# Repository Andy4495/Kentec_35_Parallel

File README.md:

# Kentec EB-LM4F120-L35 BoosterPack Library

This library supports the Kentec [EB-LM4F120-L35][4] 3.5" QVGA TFT LCD BoosterPack with Parallel I/O.

The EB-LM4F120-L35 uses the same display and controller chip as the SPI-based [BOOSTXL-K350QVG-S1][5] BoosterPack.

The parallel I/O of the LM4F120 version of the BoosterPack allows faster screen drawing with the disadvantage of requiring more I/O pins. Although the name implies that it was designed for the Stellaris ARM-based LaunchPad, it will work with MSP430-based LaunchPads that have the 40-pin BOOSTXL interface and enough RAM to support using a large display.

This library is optimized for use with the [MSP430F5529][9] and [MSP432P401R][10] LaunchPads, but will also work with any other MSP or Tiva LaunchPad with the BOOSTXL interface. Display refresh rates on boards other than the F5529 or MSP432 will be much slower due to the use of the generic `DigitalWrite()` for I/O control. When used with the F5529 or MSP432, the library uses a much faster direct register control for I/O.

This library is based on the [Kentec_35_SPI library][8] which is included with Energia.

The screen touch functionality was carried over from the SPI version of the library and the I/O pin number definitions were updated accordingly. However, touch functionality has not been tested with this library.

## Usage

See the sketch included in the `examples` folder.

The parallel library works the same as the built-in SPI version of the library. See the [Reference Manual][12] included with the library.

## Specialized Interface Board

I created a custom interface board to change the mapping of the pins between the Kentec BoosterPack and the F5529 LaunchPad. This was done for two reasons:

- Directly map the data bit positions of the Kentec controller interface to the MSP port bit positions. This allows simplification of the library code to allow even faster screen refresh rates.
- Move the Kentec pins to the inner BOOSTXL header pins (J3 and J4), so that the standard BoosterPack I/O pins are available for other devices (e.g. SPI and I2C pins).

Details on the board design can be found in the [extras/Hardware][11] folder.

The library has been modified to support the interface board. When using the library with the interface, the only code change needed is in the constructor to let the library know that the interface board is connected. By default, the TOUCH functionality is not connected when using the interface board:

    Screen_K35_Parallel myScreen(Screen_K35_Parallel::F5529_INTERFACE_BOARD_INSTALLED, Screen_K35_Parallel::TOUCH_DISABLED);

If, however, you connect the TOUCH sensor pins (XP->P2, YP->P6, XN->P12, YN->P11), then use the following constructor:

    Screen_K35_Parallel myScreen(Screen_K35_Parallel::F5529_INTERFACE_BOARD_INSTALLED, Screen_K35_Parallel::TOUCH_ENABLED);

## References

- EB-LM4F120-L35 BoosterPack [product page][4]
- EB-LM4F120-L35 BoosterPack [user guide][1]
- SSD2119 driver chip [datasheet][2]
- [Review][3] of the EB-LM4F120-L35 from Rei Vilo's Embedded Computing site.
- Kentec_35_SPI library suite [description][8] and [source][6].
- BOOSTXL-K350QVG-S1 (SPI) [product page][7]

## License

This library is based off of code by Rei VILO, <https://embedxcode.weebly.com>, <https://github.com/energia/msp430-lg-core/tree/master/libraries/Kentec_35_SPI>.

The software and other files in this repository are licensed for hobbyist and personal use under the Creative Commons License [CC BY-NC-SA 3.0][100]. See the file [`LICENSE`][101] in this repository.

[1]: ./extras/Kentec%20Parallel%20LCD%20EB-LM4F120-L35_UserGuide_04.pdf
[2]: https://support.newhavendisplay.com/hc/en-us/article_attachments/4414860088727
[3]: https://embeddedcomputing.weebly.com/kentec-35-lcd-with-touch-boosterpack-for-stellaris.html
[4]: https://www.newark.com/kentec-display/eb-lm4f120-l35/exp-board-lcd-boosterpack-stellaris/dp/48W2063
[5]: http://www.ti.com/tool/BOOSTXL-K350QVG-S1
[6]: https://github.com/energia/msp430-lg-core/tree/master/libraries/Kentec_35_SPI
[7]: http://www.ti.com/tool/BOOSTXL-K350QVG-S1
[8]: https://embeddedcomputing.weebly.com/lcd_screen-library-suite.html
[9]: http://www.ti.com/tool/MSP-EXP430F5529LP
[10]: http://www.ti.com/tool/MSP-EXP432P401R
[11]: ./extras/Hardware
[12]: ./extras/LCD_screen-ReferenceManual.pdf
[100]: https://creativecommons.org/licenses/by-nc-sa/3.0/
[101]: ./LICENSE
[//]: # ([200]: https://github.com/Andy4495/Kentec_35_Parallel)
[//]: # ( http://www.kentecdisplay.com/uploads/soft/Products_spec/EB-LM4F120-L35_UserGuide_04.pdf )
[//]: # ( http://www.kentecdisplay.com/uploads/soft/Datasheet/SSD2119_1.4.pdf )
[//]: # ( http://www.kentecdisplay.com/plus/view.php?aid=71 )

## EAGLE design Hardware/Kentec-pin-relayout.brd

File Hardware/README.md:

Specialized Interface Board
===========================
I created a custom interface board to change the mapping of the pins between the Kentec BoosterPack and the F5529 LaunchPad. This was done for two reasons:
- Directly map the data bit positions of the Kentec controller interface to the MSP port bit positions. This allows simplification of the library code to allow even faster screen refresh rates.
- Move the Kentec pins to the inner BOOSTXL header pins (J3 and J4), so that the standard BoosterPack I/O pins are available for other devices (e.g. SPI and I2C pins).

Interface Board Details
-----------------------
The interface board is specific to the MSP430F5529 LaunchPad and re-maps the Kentec BoosterPack pins as follows:

    Signal    F5529    LaunchPad
    ------    -----    ---------
    LCD_D0     P6.0       23
    LCD_D1     P6.1       24
    LCD_D2     P6.2       25
    LCD_D3     P6.3       26
    LCD_D4     P6.4       27
    LCD_D5     P3.5       30
    LCD_D6     P3.6       29
    LCD_D7     P3.7       32
    LCD_RD     P2.6       13
    LCD_WR     P1.5       38
    LCD_RS     P1.4       37       Also referred to as LCD_DS
    LCD_CS     P1.3       36

In addition, header pins are provided for the TOUCH functionality. These should be connected as follows if using TOUCH (headers for the corresponding LauncPad pins are provided next to the TOUCH headers on the PCB):

     Signal    F5529    LaunchPad
    --------   -----    ---------
    TOUCH_XP    P6.5        2       Analog pin A5
    TOUCH_YP    P6.6        6       Analog pin A6
    TOUCH_XN    P2.3       12
    TOUCH_YN    P8.1       11

Header pins are provided for the other LaunchPad pins, including:
- Vcc (3.3V and 5.0V)
- Ground
- I2C
- SPI
- Other unused I/O pins

Finally, space is provided for a 3.3V regulator (and caps), micro USB power connector, 3 general-purpose switches, and a reset switch. 

Library Support
---------------

The library has been modified to support the interface board. When using the library with the interface, the only code change needed is in the constructor to let the library know that the interface board is connected. By default, the TOUCH functionality is not connected when using the interface board:

    Screen_K35_Parallel myScreen(Screen_K35_Parallel::F5529_INTERFACE_BOARD_INSTALLED, Screen_K35_Parallel::TOUCH_DISABLED);

If, however, you connect the TOUCH sensor pins (XP->P2, YP->P6, XN->P12, YN->P11), then use the following constructor:

    Screen_K35_Parallel myScreen(Screen_K35_Parallel::F5529_INTERFACE_BOARD_INSTALLED, Screen_K35_Parallel::TOUCH_ENABLED);

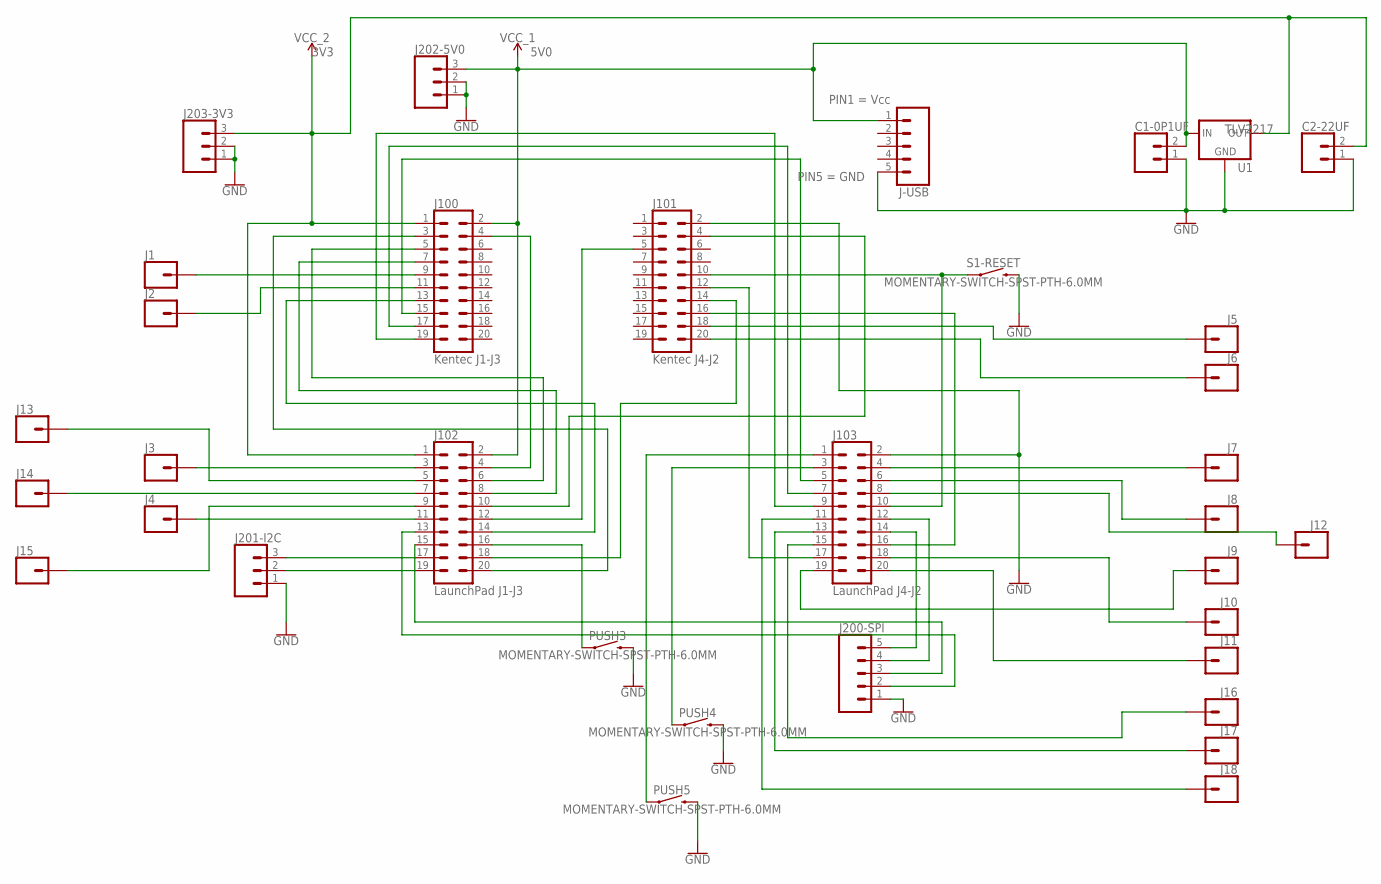
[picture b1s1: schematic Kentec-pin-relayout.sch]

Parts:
C1-0P1UF, C2-22UF: CONN_02; 1X02
J1, J2, J3, J4, J5, J6, J7, J8, J9, J10, J11, J12, J13, J14, J15, J16, J17, J18: CONN_01; 1X01
J100: Kentec J1-J3; 2X10_LOCK
J101: Kentec J4-J2; 2X10_LOCK
J102: LaunchPad J1-J3; 2X10_LOCK
J103: LaunchPad J4-J2; 2X10_LOCK
J200-SPI: CONN_05LOCK; 1X05_LOCK
J201-I2C, J202-5V0, J203-3V3: CONN_03LOCK; 1X03_LOCK
J-USB: CONN_05LOCK; 1X05_LOCK
PUSH3, PUSH4, PUSH5: MOMENTARY-SWITCH-SPST-PTH-6.0MM; TACTILE_SWITCH_PTH_6.0MM
S1-RESET: MOMENTARY-SWITCH-SPST-PTH-6.0MM; TACTILE_SWITCH_PTH_6.0MM
U1: V_REG_78XX-TO-220; TO-220-ALT

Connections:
GND: C1-0P1UF.1, C2-22UF.1, J101.2, J103.2, J200-SPI.1, J201-I2C.1, J202-5V0.1, J202-5V0.2, J203-3V3.1, J203-3V3.2, J-USB.5, PUSH3.3 (2), PUSH4.3 (2), PUSH5.3 (2), S1-RESET.3 (2), U1.GND
unnamed: J100.5, J102.6
unnamed: J100.7, J102.8
unnamed: J101.4, J102.10
unnamed: J101.5, J102.12
unnamed: J100.13, J102.14
unnamed: J100.3, J102.20
unnamed: J101.14, J102.18
unnamed: J101.12, J103.17
unnamed: J100.15, J103.5
unnamed: J100.17, J103.7
unnamed: J100.19, J103.9
unnamed: J101.10, J103.10, S1-RESET.1
unnamed: J102.15, J200-SPI.3
unnamed: J102.13, J200-SPI.2
unnamed: J100.4, J102.4
unnamed: J1.1, J100.9
unnamed: J2.1, J100.11
unnamed: J5.1, J101.18
unnamed: J102.16, PUSH3.1
unnamed: J103.3, PUSH4.1
unnamed: J103.1, PUSH5.1
unnamed: J102.17, J201-I2C.3
unnamed: J102.19, J201-I2C.2
unnamed: J103.14, J200-SPI.5
unnamed: J103.12, J200-SPI.4
unnamed: J6.1, J101.20
unnamed: J3.1, J102.3
unnamed: J4.1, J102.11
unnamed: J7.1, J103.4
unnamed: J8.1, J103.6
unnamed: J101.16, J103.16
unnamed: J10.1, J103.18
unnamed: J12.1, J103.8
unnamed: J11.1, J103.20
unnamed: J14.1, J102.7
unnamed: J13.1, J102.5
unnamed: J15.1, J102.9
unnamed: J9.1, J103.19
unnamed: J16.1, J103.15
unnamed: J17.1, J103.13
unnamed: J18.1, J103.11
VCC_1: C1-0P1UF.2, J100.2, J102.2, J202-5V0.3, J-USB.1, U1.IN
VCC_2: C2-22UF.2, J100.1, J102.1, J203-3V3.3, U1.OUT

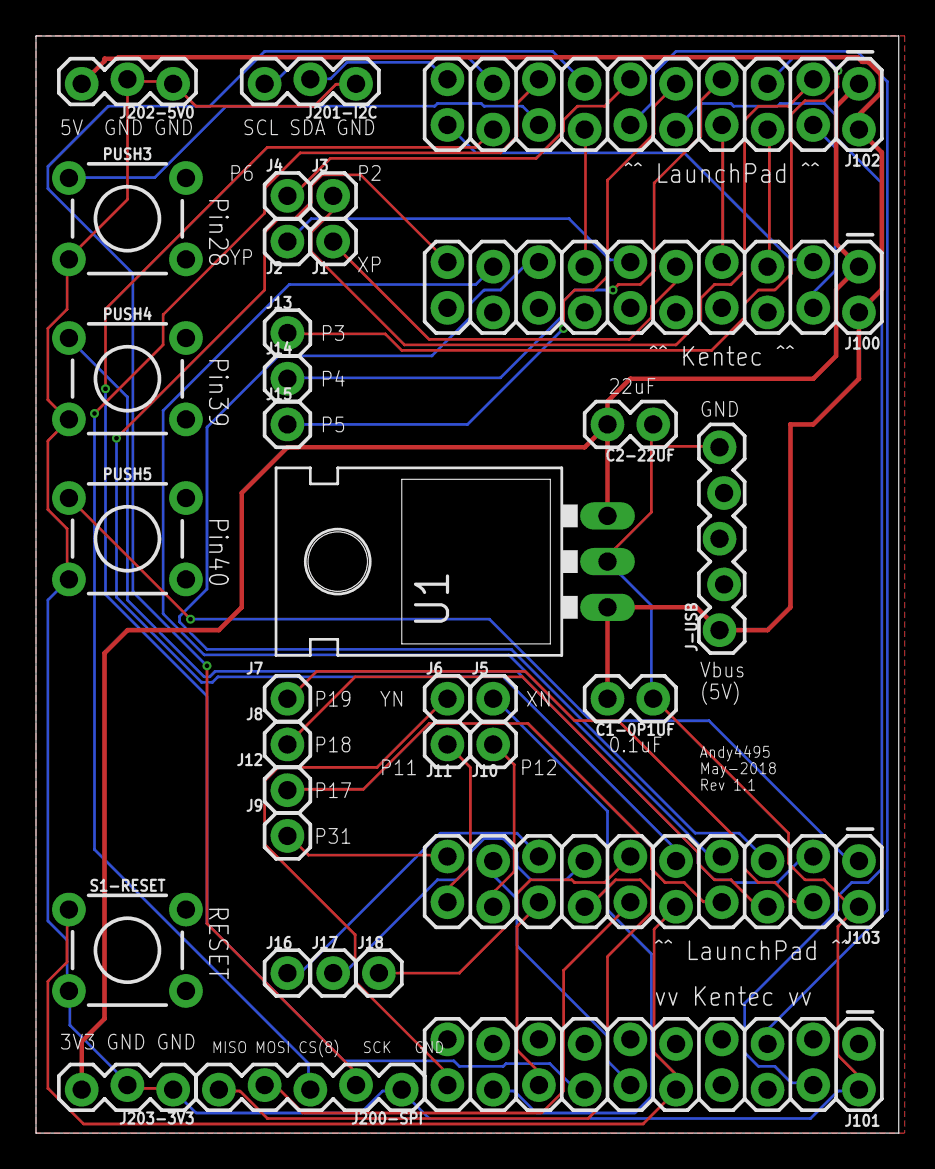
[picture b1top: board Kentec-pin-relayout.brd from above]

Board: 2 copper layers, 47.9 x 61.0 mm, 34 parts (0 on the bottom side), 44 nets.

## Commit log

2018-04-09 Initial commit.
2018-04-09 Direct Port IO for F5529 and other speed optimizations.
2018-04-09 Optimizing code for F5529.
2018-04-10 Further optimization using lookup table.
2018-04-11 Optimization with 256-byte lookup table.
2018-04-11 Clean up comments.
2018-04-13 Merged in with original SPI code files for easier diff.
2018-04-14 Update README, update comments for Reset pin.
2018-04-15 Add fast I/O hardware support for MSP432P401R.
2018-04-16 Fix link.
2018-04-26 Simplified digitalWrite() IO used by non-F5529, MSP432 LaunchPads.
2018-04-26 Fix GitLab URL. No functional changes.
2018-05-11 Add support for specialized F5529 interface board.
2018-05-17 Move _touch_feature def outside of #ifdef.
2019-11-12 Update gitlab references to github.
2019-11-15 Update version since repository URL changed.
2020-01-09 Update directory structure to move Hardware under extras folder.
2021-04-14 Add license info.
2021-04-14 Update LICENSE
2021-04-30 Clean up markdownlint issues.
2022-02-25 Add .gitignore
2022-03-21 Add workflow
2022-06-23 Convert to full library structure
2022-06-23 Add compile badge
2022-07-12 Remove unnecessary files
2022-08-04 Compatibility with Arduino IDE/CLI
2022-09-08 markdownlint issues
2023-08-24 Update for nektos/act compatibility
2023-08-30 nektos/act compatibility
2023-09-05 Change to reusable workflows
2023-09-17 Add create-release workflow
2024-03-08 Update cron time
2024-09-27 Use new Package Index JSON Files
2024-09-30 Switch to lychee for link checks
2024-10-01 add extra-input-files to catch all the .md files
2024-10-01 Add default to extra-input-files
2024-10-01 ./extras/**/*.md is now included in base action
2025-01-02 Add GCC9 to compile matrix
2025-02-04 Clean up dead links

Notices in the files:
parts and their libraries:
SparkFun-Connectors: Licensing: Creative Commons ShareAlike 4.0 International - https://creativecommons.org/licenses/by-sa/4.0
